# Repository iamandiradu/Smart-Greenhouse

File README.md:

Smart Greenhouse

A project by Radu Iamandi

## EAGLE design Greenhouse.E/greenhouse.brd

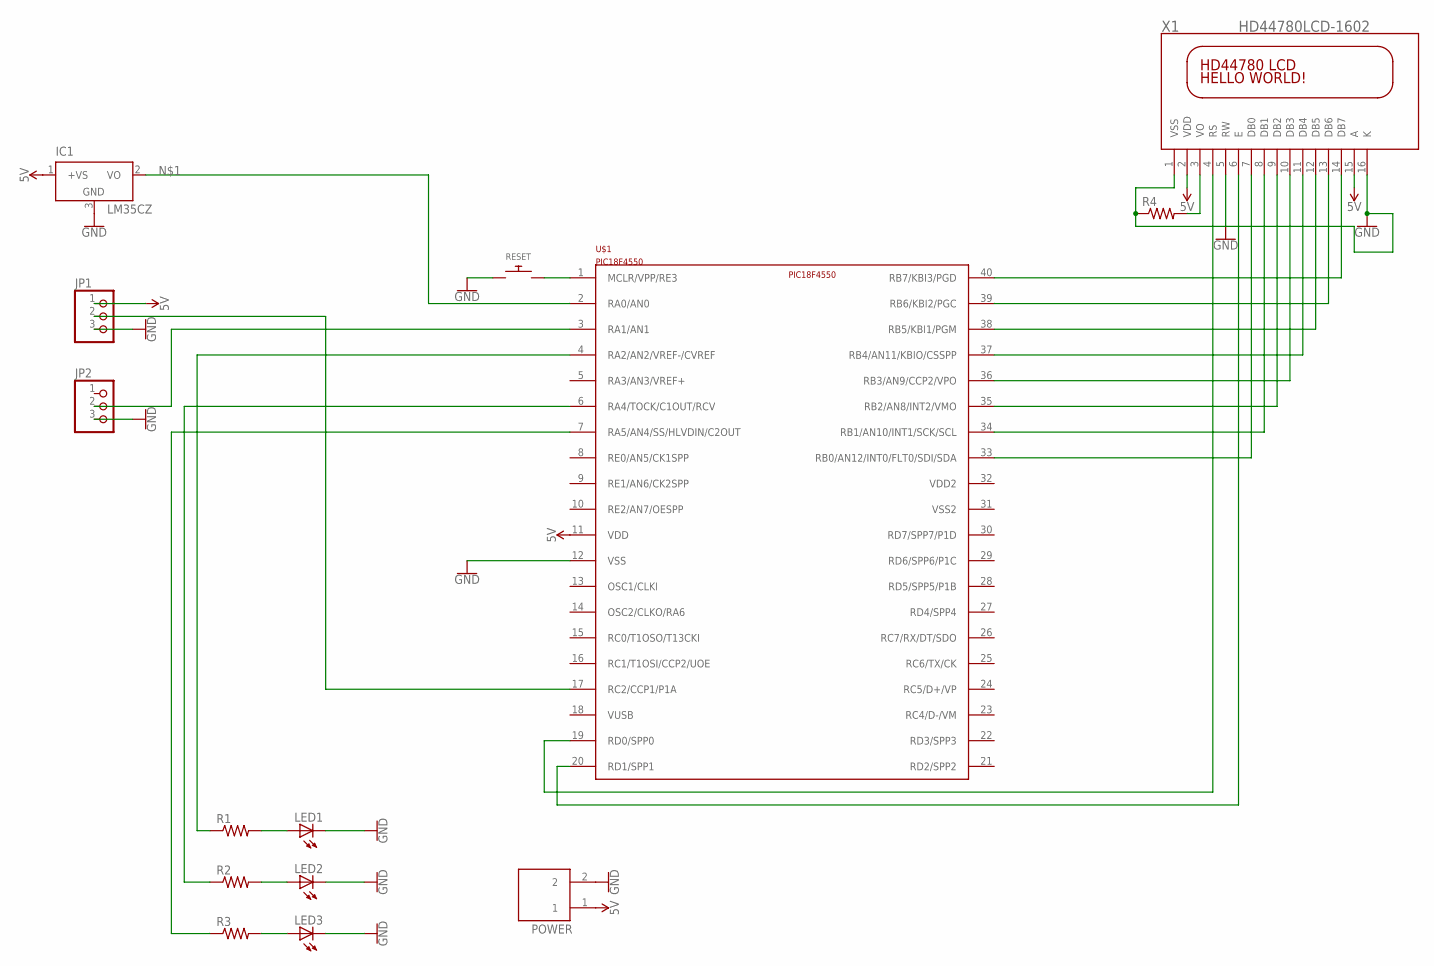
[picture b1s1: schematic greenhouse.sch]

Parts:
IC1: LM35CZ; TO92
JP1, JP2: PINHD-1X3; 1X03
LED1, LED2, LED3: LED5MM
POWER: ED555/2DS
R1, R2, R3, R4: R-US_0204/2V; 0204V
RESET: SWITCH_PUSHBUTTONEVQ-PE; TACT_PANA-EVQ
U$1: PIC18F4550; PDIP-40
X1: HD44780LCD-1602; LCD1602

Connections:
5V: IC1.1 (+VS), JP1.1, POWER.1, U$1.11 (VDD), X1.15 (A)
GND: IC1.3 (GND), JP1.3, JP2.3, LED1.K (C), LED2.K (C), LED3.K (C), POWER.2, R4.1, RESET.P$1, U$1.12 (VSS), X1.1 (VSS), X1.16 (K)
unnamed: IC1.2 (VO), U$1.2 (RA0/AN0)
unnamed: JP1.2, U$1.17 (RC2/CCP1/P1A)
unnamed: JP2.2, U$1.3 (RA1/AN1)
unnamed: R4.2, X1.3 (VO)
unnamed: U$1.40 (RB7/KBI3/PGD), X1.14 (DB7)
unnamed: U$1.39 (RB6/KBI2/PGC), X1.13 (DB6)
unnamed: U$1.20 (RD1/SPP1), X1.6 (E)
unnamed: U$1.19 (RD0/SPP0), X1.4 (RS)
unnamed: U$1.38 (RB5/KBI1/PGM), X1.12 (DB5)
unnamed: U$1.37 (RB4/AN11/KBIO/CSSPP), X1.11 (DB4)
unnamed: LED1.A, R1.2
unnamed: LED2.A, R2.2
unnamed: LED3.A, R3.2
unnamed: R1.1, U$1.4 (RA2/AN2/VREF-/CVREF)
unnamed: R2.1, U$1.6 (RA4/TOCK/C1OUT/RCV)
unnamed: R3.1, U$1.7 (RA5/AN4/SS/HLVDIN/C2OUT)
unnamed: RESET.P$2, U$1.1 (MCLR/VPP/RE3)
unnamed: U$1.36 (RB3/AN9/CCP2/VPO), X1.10 (DB3)
unnamed: U$1.35 (RB2/AN8/INT2/VMO), X1.9 (DB2)
unnamed: U$1.34 (RB1/AN10/INT1/SCK/SCL), X1.8 (DB1)
unnamed: U$1.33 (RB0/AN12/INT0/FLT0/SDI/SDA), X1.7 (DB0)
VDD: X1.2 (VDD)
VDD2: U$1.32 (VDD2)
VSS2: U$1.31 (VSS2)

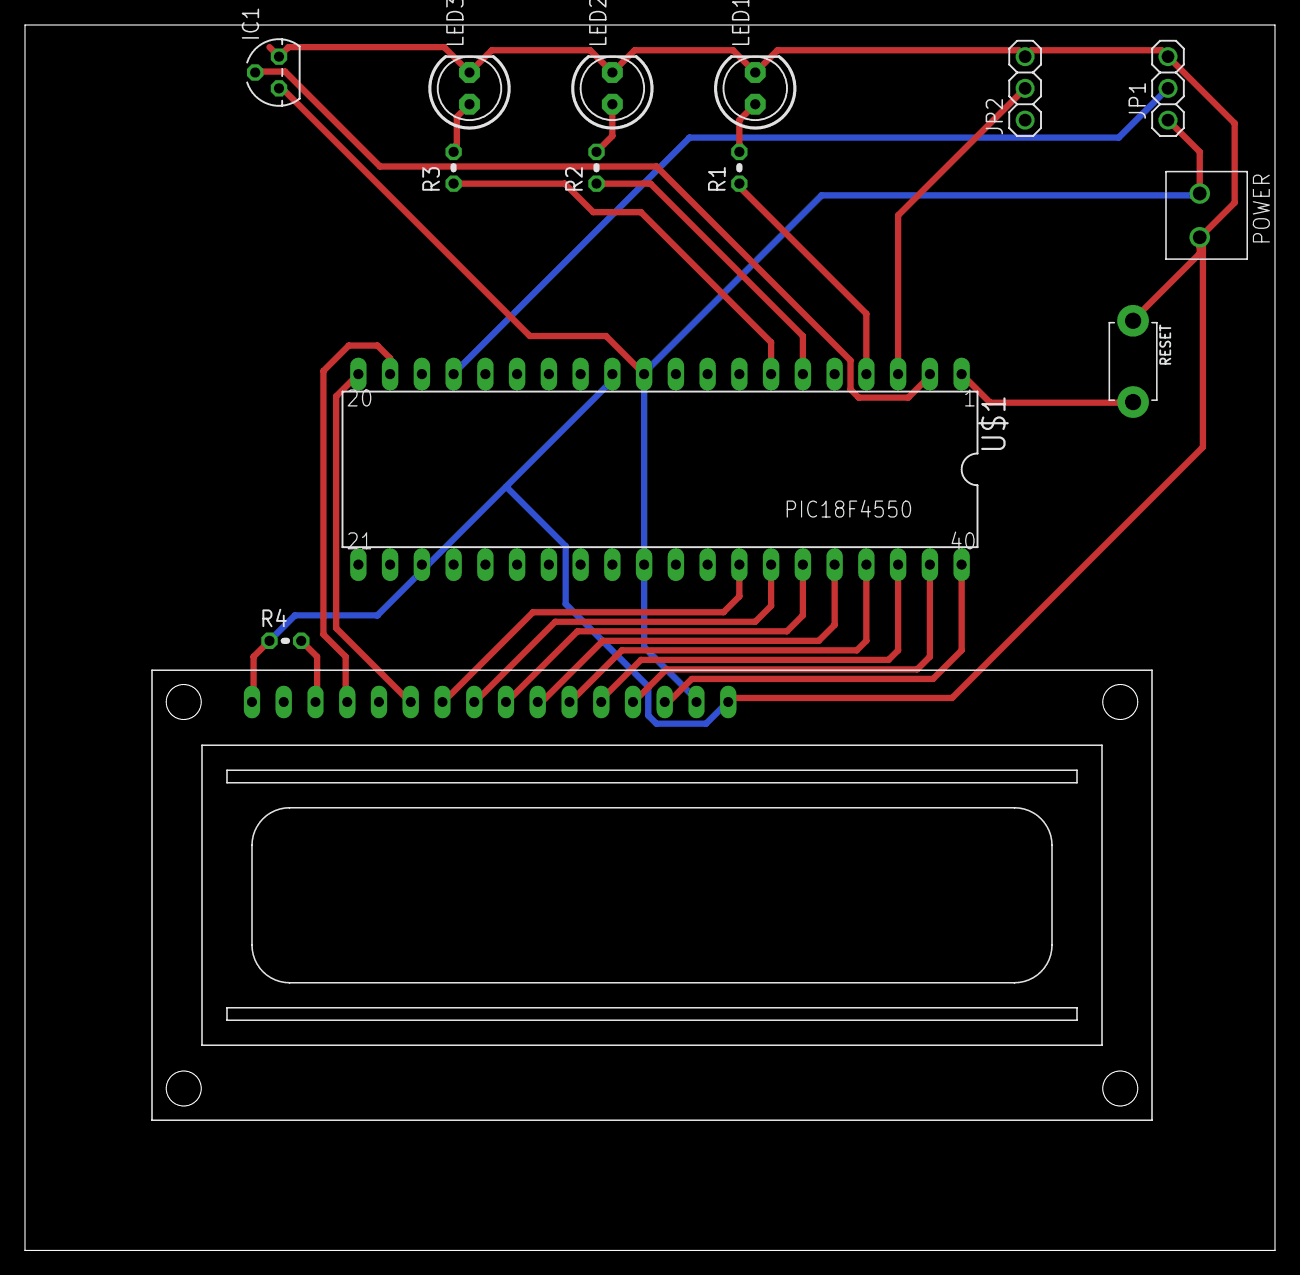
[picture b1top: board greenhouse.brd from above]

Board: 2 copper layers, 100.0 x 98.0 mm, 14 parts (0 on the bottom side), 23 nets.

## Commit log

2019-06-02 Fully working state; needs cleanup
2019-06-03 Final version
2019-06-03 Add layout

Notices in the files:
parts and their libraries:
SparkFun-PowerSymbols: Licensing: Creative Commons ShareAlike 4.0 International - https://creativecommons.org/licenses/by-sa/4.0
